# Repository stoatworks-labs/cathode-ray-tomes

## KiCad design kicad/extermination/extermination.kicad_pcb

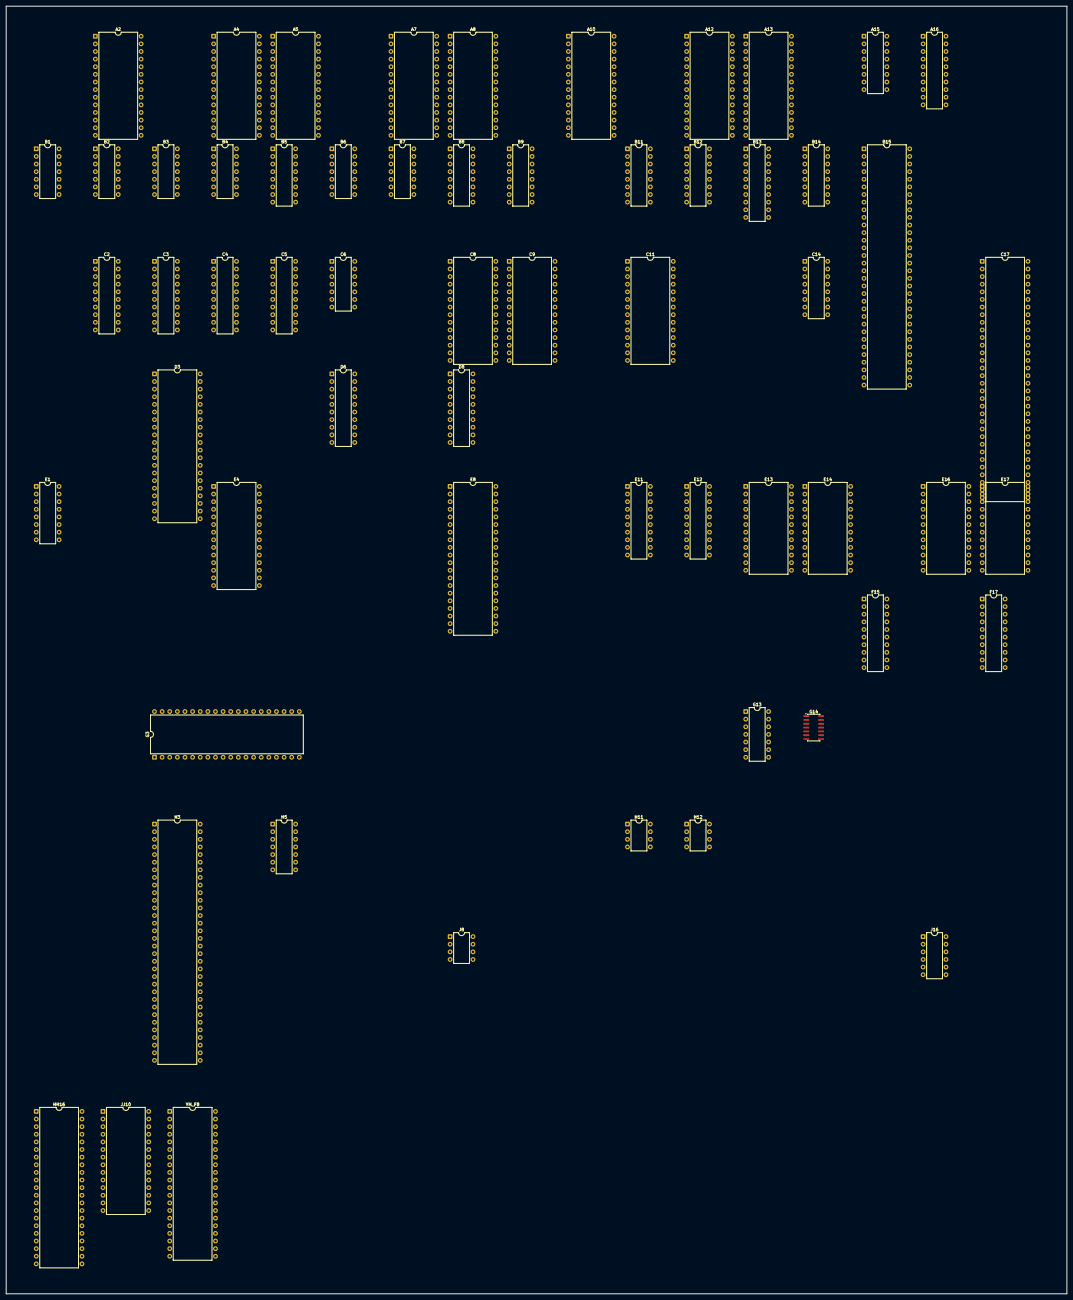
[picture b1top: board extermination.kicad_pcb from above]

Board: 2 copper layers, 353.4 x 429.0 mm, 60 parts (0 on the bottom side), 301 nets, no tracks yet.

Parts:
A2, A4, A5, A7, A8, A10, A12, A13: 27C512; DIP-28_W15.24mm
A15: 74LS174; DIP-16_W7.62mm
A16: 74LS273; DIP-20_W7.62mm
B1: 74LS04; DIP-14_W7.62mm
B2, B6: 74LS08; DIP-14_W7.62mm
B3, B4, B7: 74LS74; DIP-14_W7.62mm
B5: 74LS174; DIP-16_W7.62mm
B8, B9, B11, B12: 74LS157; DIP-16_W7.62mm
B13: 74LS245; DIP-20_W7.62mm
B14: 74LS367; DIP-16_W7.62mm
B15: YM3909; DIP-64_W15.24mm
C2, C3: PAL16L8; DIP-20_W7.62mm
C4, C5: 74LS245; DIP-20_W7.62mm
C6: 74LS32; DIP-14_W7.62mm
C8: MB8464A-10L-LL; DIP-28_W15.24mm
C9, C11: 27C512; DIP-28_W15.24mm
C14: 74LS367; DIP-16_W7.62mm
C17: YM3906; DIP-64_W15.24mm
D3: Z80CPU; DIP-40_W15.24mm
D6, D8: PAL16L8; DIP-20_W7.62mm
E1: 74LS174; DIP-16_W7.62mm
E4: 27C512; DIP-28_W15.24mm
E8: Z80CPU; DIP-40_W15.24mm
E11, E12: 74LS245; DIP-20_W7.62mm
E13, E14, E16, E17: HM6116P-3; DIP-24_W15.24mm
F15, F17: MB7124E; DIP-20_W7.62mm
G3: INTEL8742; DIP-40_W15.24mm
G13: 74LS04; DIP-14_W7.62mm
G14: 74HC4024; SOIC-14_3.9x8.7mm_P1.27mm
H3: SETA-X1-004; DIP-64_W15.24mm
H5: 74LS02; DIP-14_W7.62mm
H11: YM3014; DIP-8_W7.62mm
H12: NJM4558; DIP-8_W7.62mm
HH16: SETAX1-003; DIP-42_W15.24mm
J8: TL7705A; DIP-8_W7.62mm
J16: HA1388; DIP-12_W7.62mm
JJ10: PC050CM; DIP-28_W15.24mm
YM_F8: YM2203; DIP-40_W15.24mm

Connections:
/CI/O1: H3.23, JJ10.3
/CI/O2: H3.22, JJ10.14
/DATAEN: B15.4, C17.61
/GDA0: A12.11, A13.11, B15.56
/GDA1: A12.12, A13.12, B15.57
/GDA2: A12.13, A13.13, B15.58
/GDA3: A12.15, A13.15, B15.59
/GDA4: A12.16, A13.16, B15.60
/GDA5: A12.17, A13.17, B15.61
/GDA6: A12.18, A13.18, B15.62
/GDA7: A12.19, A13.19, B15.63
/GDB0: A8.11, A10.11, B15.48
/GDB1: A8.12, A10.12, B15.49
/GDB2: A8.13, A10.13, B15.50
/GDB3: A8.15, A10.15, B15.51
/GDB4: A8.16, A10.16, B15.52
/GDB5: A8.17, A10.17, B15.53
/GDB6: A8.18, A10.18, B15.54
/GDB7: A8.19, A10.19, B15.55
/GDC0: A5.11, A7.11, B15.40
/GDC1: A5.12, A7.12, B15.41
/GDC2: A5.13, A7.13, B15.42
/GDC3: A5.15, A7.15, B15.43
/GDC4: A5.16, A7.16, B15.44
/GDC5: A5.17, A7.17, B15.45
/GDC6: A5.18, A7.18, B15.46
/GDC7: A5.19, A7.19, B15.47
/GDD0: A2.11, A4.11, B15.30
/GDD1: A2.12, A4.12, B15.31
/GDD2: A2.13, A4.13, B15.34
/GDD3: A2.15, A4.15, B15.35
/GDD4: A2.16, A4.16, B15.36
/GDD5: A2.17, A4.17, B15.37
/GDD6: A2.18, A4.18, B15.38
/GDD7: A2.19, A4.19, B15.39
/GFXA_~CS: D6.18, E13.18
/GFXB_~CS: D6.17, E14.18
/GFXC_~CS: D6.16, E16.18
/GFXD_~CS: D6.15, E17.18
/GFX_CLK: B15.3, C17.62
/GFX_~CE: B6.6, C6.1
/H0: B13.4, B13.5, B13.6, C17.40
/H0_BUF: B3.3, B3.11, B7.11, B13.15, D3.6
/H1: B13.7, C17.39
/H1_BUF: B13.13, G3.2, G13.11
/H2: B13.2, C17.41
/H2_BUF: B2.4, B13.18, YM_F8.38
/H3: B1.1, B13.8, C17.42
/H3_BUF: B2.5, B13.12, B14.1, B14.15, C6.2, C6.13, C14.1, C14.15, D6.11
/H4: B13.9, C17.43
/H4_BUF: A15.9, A16.11, B13.11
/HC0: B15.19, C17.46
/HC1: B15.18, C17.47
/HC2: B15.17, C17.48
/HC3: B15.16, C17.49
/HC4: B15.15, C17.50
/HC5: B15.14, C17.51
/HC6: B15.13, C17.52
/HC7: B15.12, C17.53
/HC8: B15.11, C17.54
/MAIN_A0: B12.10, B14.10, C9.10, C11.10, E8.30
/MAIN_A1: B12.13, B14.12, C9.9, C11.9, E8.31
/MAIN_A2: B9.3, B14.14, C9.8, C11.8, E8.32
/MAIN_A3: B11.13, B14.2, C9.7, C11.7, E8.33
/MAIN_A4: B12.3, B14.4, C9.6, C11.6, E8.34
/MAIN_A5: B12.6, B14.6, C9.5, C11.5, E8.35
/MAIN_A6: B11.10, C9.4, C11.4, C14.4, E8.36
/MAIN_A7: B11.6, C9.3, C11.3, C14.6, E8.37
/MAIN_A8: B8.3, C9.25, C11.25, C14.10, E8.38
/MAIN_A9: B8.6, C9.24, C11.24, C14.12, D8.7, E8.39
/MAIN_A10: B9.10, C9.21, C11.21, C14.14, D8.6, E8.40
/MAIN_A11: B11.3, C9.23, C11.23, C17.27, D8.5, E8.1
/MAIN_A12: B9.13, C9.2, C11.2, D8.4, E8.2
/MAIN_A13: C8.26, C9.26, C11.26, D8.3, E8.3
/MAIN_A14: D6.2, D8.2, E8.4
/MAIN_A15: B2.10, D6.1, D8.1, E8.5
/MAIN_D0: E8.14, E11.3, E12.3
/MAIN_D1: E8.15, E11.2, E12.2
/MAIN_D2: E8.12, E11.9, E12.9
/MAIN_D3: E8.8, E11.8, E12.8
/MAIN_D4: E8.7, E11.7, E12.7
/MAIN_D5: E8.9, E11.6, E12.6
/MAIN_D6: E8.10, E11.5, E12.5
/MAIN_D7: E8.13, E11.4, E12.4
/MAIN_VD8: B5.3, C5.9, C9.11, C11.11
/MAIN_VD9: B5.4, C5.8, C9.12, C11.12
/MAIN_VD10: B5.6, C5.7, C9.13, C11.13
/MAIN_VD11: B5.14, C5.6, C9.15, C11.15
/MAIN_VD12: B5.13, C5.5, C9.16, C11.16
/MAIN_VD13: B5.11, C5.4, C9.17, C11.17
/MAIN_VD14: C5.3, C9.18, C11.18
/MAIN_VD15: C5.2, C9.19, C11.19
/MAIN_~RD: B1.9, B8.10, C5.1, C17.2, E8.21, E11.1, E12.1
/P10: G3.27, H3.28, H3.44
/P11: G3.28, H3.29, H3.45
/P12: G3.29, H3.30, H3.46
/P13: G3.30, H3.31, H3.47
/P14: G3.31, H3.32, H3.48
/P15: G3.32, H3.33, H3.49
/P16: G3.33, H3.34, H3.50
/P17: G3.34, H3.35, H3.51
/P20: G3.21, H3.37
/P21: G3.22, H3.41
/P22: G3.23, H3.40
/P26_DRQ: G3.37, H5.2
/RAM_~CS1: C3.17, C8.20
/RAM_~WE: C3.18, C8.27
/RESET: H5.3, H5.6, H5.9, H5.12, J8.6
/SND_A0: B12.11, D3.30, E4.10, G3.9, YM_F8.37
/SND_A1: B12.14, D3.31, E4.9
/SND_A2: B9.2, D3.32, E4.8
/SND_A3: B11.14, D3.33, E4.7
/SND_A4: B12.2, D3.34, E4.6
/SND_A5: B12.5, D3.35, E4.5
/SND_A6: B11.11, D3.36, E4.4
/SND_A7: B11.5, D3.37, E4.3
/SND_A8: B8.2, D3.38, E4.25
/SND_A9: B8.5, D3.39, E4.24
/SND_A10: B9.11, D3.40, E4.21
/SND_A11: B11.2, C2.5, D3.1, E4.23
/SND_A12: B9.14, C2.4, D3.2, E4.2
/SND_A13: C2.3, D3.3
/SND_A14: C2.2, D3.4
/SND_A15: C2.1, D3.5, E4.1
/SND_D0: C4.9, D3.14, E1.14, E4.11, G3.12, YM_F8.40
/SND_D1: C4.8, D3.15, E1.13, E4.12, G3.13, YM_F8.2
/SND_D2: C4.7, D3.12, E1.11, E4.13, G3.14, YM_F8.3
/SND_D3: C4.6, D3.8, E1.6, E4.15, G3.15, YM_F8.4
/SND_D4: C4.5, D3.7, E1.4, E4.16, G3.16, YM_F8.5
/SND_D5: C4.4, D3.9, E1.3, E4.17, G3.17, YM_F8.6
/SND_D6: C4.3, D3.10, E4.18, G3.18, YM_F8.7
/SND_D7: C4.2, D3.13, E4.19, G3.19, YM_F8.8
/SND_~RD: B8.11, C4.1, D3.21, G3.8, YM_F8.36
/SND_~WAIT: C3.13, D3.24
/SND_~WR: C2.6, C3.4, D3.22, G3.10, YM_F8.35
/SYNC: HH16.22, HH16.23
/VA0: B14.9, C17.15, E13.8, E14.8, E16.8, E17.8
/VA1: B14.11, C17.16, E13.7, E14.7, E16.7, E17.7
/VA2: B14.13, C17.17, E13.6, E14.6, E16.6, E17.6
/VA3: B14.3, C17.18, E13.5, E14.5, E16.5, E17.5
/VA4: B14.5, C17.19, E13.4, E14.4, E16.4, E17.4
/VA5: B14.7, C17.20, E13.3, E14.3, E16.3, E17.3
/VA6: C14.5, C17.21, E13.2, E14.2, E16.2, E17.2
/VA7: C14.7, C17.22, E13.1, E14.1, E16.1, E17.1
/VA8: C14.9, C17.23, E13.23, E14.23, E16.23, E17.23
/VA9: C14.11, C17.24, E13.22, E14.22, E16.22, E17.22
/VA10: C14.13, C17.25, E13.19, E14.19, E16.19, E17.19
/VA11: C17.28, D6.7
/VBLK: B1.12, B4.3
/VD0: A15.4, C17.4, E12.17, E13.9, E14.9
/VD1: A15.3, E12.18, E13.10, E14.10
/VD2: A15.14, B15.10, E12.11, E13.11, E14.11
/VD3: A15.13, B15.9, E12.12, E13.13, E14.13
/VD4: A15.11, B15.8, E12.13, E13.14, E14.14
/VD5: A15.6, B15.7, E12.14, E13.15, E14.15
/VD6: B15.6, C17.59, E12.15, E13.16, E14.16
/VD7: B15.5, C17.60, E12.16, E13.17, E14.17
/VD8: A16.14, C17.14, E11.17, E16.9, E17.9
/VD9: A16.17, C17.13, E11.18, E16.10, E17.10
/VD10: A16.3, C17.12, E11.11, E16.11, E17.11
/VD11: A16.4, C17.11, E11.12, E16.13, E17.13
/VD12: A16.7, C17.10, E11.13, E16.14, E17.14
/VD13: A16.8, C17.9, E11.14, E16.15, E17.15
/VD14: A16.13, C17.8, E11.15, E16.16, E17.16
/VD15: A16.18, C17.7, E11.16, E16.17, E17.17
/WATCHDOG: B1.6, G14.2
/colmix/COL0: B15.20, F15.1, F17.1
/colmix/COL1: B15.21, F15.2, F17.2
/colmix/COL2: B15.22, F15.3, F17.3
/colmix/COL3: B15.23, F15.4, F17.4
/colmix/COL4: B15.24, F15.5, F17.5
/colmix/COL5: B15.25, F15.16, F17.16
/colmix/COL6: B15.26, F15.17, F17.17
/colmix/COL7: B15.27, F15.18, F17.18
/colmix/COL8: B15.28, F15.19, F17.19
/gfx/GA0: A2.10, A4.10, A5.10, A7.10, A8.10, A10.10, A12.10, A13.10, C17.35
/gfx/GA1: A2.9, A4.9, A5.9, A7.9, A8.9, A10.9, A12.9, A13.9, C17.36
/gfx/GA2: A2.8, A4.8, A5.8, A7.8, A8.8, A10.8, A12.8, A13.8, C17.37
/gfx/GA4: A2.6, A4.6, A5.6, A7.6, A8.6, A10.6, A12.6, A13.6, C17.38
/gfx/GA5: A2.5, A4.5, A5.5, A7.5, A8.5, A10.5, A12.5, A13.5, A16.15
/gfx/GA6: A2.4, A4.4, A5.4, A7.4, A8.4, A10.4, A12.4, A13.4, A16.16
/gfx/GA7: A2.3, A4.3, A5.3, A7.3, A8.3, A10.3, A12.3, A13.3, A16.2
/gfx/GA8: A2.25, A4.25, A5.25, A7.25, A8.25, A10.25, A12.25, A13.25, A16.5
/gfx/GA9: A2.24, A4.24, A5.24, A7.24, A8.24, A10.24, A12.24, A13.24, A16.6
/gfx/GA10: A2.21, A4.21, A5.21, A7.21, A8.21, A10.21, A12.21, A13.21, A16.9
/gfx/GA11: A2.23, A4.23, A5.23, A7.23, A8.23, A10.23, A12.23, A13.23, A16.12
/gfx/GA12: A2.2, A4.2, A5.2, A7.2, A8.2, A10.2, A12.2, A13.2, A16.19
/gfx/GA13: A2.26, A4.26, A5.26, A7.26, A8.26, A10.26, A12.26, A13.26, A15.5
/gfx/GA14: A2.27, A4.27, A5.27, A7.27, A8.27, A10.27, A12.27, A13.27, A15.2
/gfx/GA15: A2.1, A4.1, A5.1, A7.1, A8.1, A10.1, A12.1, A13.1, A15.12
/gfx/GFX_~WR: C6.6, E13.21, E14.21, E16.21, E17.21
/gfx/HR8: A2.7, A4.7, A5.7, A7.7, A8.7, A10.7, A12.7, A13.7, C17.34
/gfx/SPBANK1: C14.3, C17.26
/gfx/gfx_rom/~ROM_CE': A2.20, A5.20, A8.20, A12.20, B1.10
/gfx/~ROM_CE: A4.20, A7.20, A10.20, A13.20, A15.10, B1.11
/gfx/~ROM_OE: A2.22, A4.22, A5.22, A7.22, A8.22, A10.22, A12.22, A13.22, A15.15
/main/BANK_CFG0: B5.2, C9.27, D6.6
/main/BANK_CFG1: B2.9, B5.5, C9.1
/main/BANK_CFG2: B5.7, D6.5
/main/MAIN_~WAIT: C3.14, E8.24
/main/MAIN_~WR: C3.2, D8.11, E8.22
/main/ROMB_A14: C11.27, D6.14
/main/ROMB_A15: B2.8, C11.1
/main/~BGTRNSP: B6.4, D8.14
/main/~MREQ: D6.3, D8.8, E8.19
/main/~OBJCODEHI: B6.5, D6.9, D8.17
/main/~RFSH: D6.4, D8.9, E8.28
/main/~RM_OEA: C9.22, D6.12
/main/~RM_OEB: C11.22, D6.13
/main/~SND_RST': B2.2, B5.12
/main/~WDOGCLR: B1.5, B5.9, D8.15
/mcu/TEST0: G3.1, JJ10.25
/mcu/TEST1: G3.39, JJ10.26
/mcu/~H1_BUF: G3.3, G13.10
/sound/RAM_~OE: B8.9, C8.22
/sound/SHA0: B12.9, C8.10
/sound/SHA1: B12.12, C8.9
/sound/SHA2: B9.4, C8.8
/sound/SHA3: B11.12, C8.7
/sound/SHA4: B12.4, C8.6
/sound/SHA5: B12.7, C8.5
/sound/SHA6: B11.9, C8.4
/sound/SHA7: B11.7, C8.3
/sound/SHA8: B8.4, C8.25
/sound/SHA9: B8.7, C8.24
/sound/SHA10: B9.9, C8.21
/sound/SHA11: B11.4, C8.23
/sound/SHA12: B9.12, C8.2
/sound/SHD0: C4.11, C5.11, C8.11
/sound/SHD1: C4.12, C5.12, C8.12
/sound/SHD2: C4.13, C5.13, C8.13
/sound/SHD3: C4.14, C5.14, C8.15
/sound/SHD4: C4.15, C5.15, C8.16
/sound/SHD5: C4.16, C5.16, C8.17
/sound/SHD6: C4.17, C5.17, C8.18
/sound/SHD7: C4.18, C5.18, C8.19
/sound/SND_CLK': B3.4, B3.9
/sound/SND_D'0: C2.11, E1.15
/sound/SND_D'1: C2.9, E1.12
/sound/SND_~INT: B7.8, D3.16
/sound/SND_~NMI: D3.17, YM_F8.25
/sound/SND_~OE: C2.12, E4.22
/sound/SND_~RFSH: C2.8, D3.28
/sound/S_~IORQ: B7.13, D3.20
/sound/S_~MREQ: C2.7, D3.19
/sound/YM_~CS: B3.2, C2.15, YM_F8.34
/sound/~SND_A14: C2.18, E4.26
/sound/~SND_A15: C2.19, E4.27
/sound/~SND_WR: C2.14, E1.9
/~COIN_LOCK: H5.1, JJ10.23
/~GFX_WR: B6.1, C17.3, D8.13
/~HBLK: C17.55, HH16.19
/~MCU_RST: B2.11, G3.4
/~OBJCODELO: B6.2, D6.8, D8.16
/~SBNKMWR: C3.16, C5.19
/~SBNKSWR: C3.15, C4.19
/~SND_CS: C2.16, G3.6
/~SND_MREQ: C2.13, C3.3
/~SND_RST: B2.3, B2.12, D3.26, E1.1, YM_F8.24
/~SND_SELECT: B8.1, B9.1, B11.1, B12.1, C3.19
/~VSYNC: C17.56, HH16.20
/~WDRES: B2.1, B5.1, C17.29, E8.26
unnamed: B1.8, C6.4
unnamed: B3.5, B3.12
unnamed: B4.6, E8.16
unnamed: B4.1, E8.20
unnamed: B2.6, B4.12
unnamed: B4.9, C3.6
unnamed: B6.3, C6.12
unnamed: B4.11, B13.17, E8.6
unnamed: C3.1, D8.18
unnamed: C3.5, D8.19
unnamed: C6.5, C17.30
unnamed: B1.13, C17.58
unnamed: G13.1, G13.4
unnamed: B2.13, E1.5
unnamed: C6.11, E11.19
unnamed: C6.3, E12.19
unnamed: G3.35, H5.11
unnamed: G3.36, H5.8
unnamed: G3.38, H5.5
unnamed: G13.3, G13.12
unnamed: G13.9, G14.5
unnamed: G13.2, G14.1
unnamed: H11.2, H12.3
unnamed: H11.3, YM_F8.22
unnamed: H11.8, H12.6, H12.7
unnamed: H11.5, YM_F8.39
unnamed: H11.7, H12.5
unnamed: H11.4, YM_F8.23
unnamed: H12.1, H12.2
unnamed: H5.4, JJ10.20
unnamed: H5.10, JJ10.8
unnamed: H5.13, JJ10.17
unnamed: YM_F8.18, YM_F8.19, YM_F8.20
unnamed: YM_F8.26, YM_F8.27
unnamed: YM_F8.28, YM_F8.29
unnamed: YM_F8.30, YM_F8.31
unnamed: YM_F8.32, YM_F8.33
VCC: A2.28, A4.28, A5.28, A7.28, A8.28, A10.28, A12.28, A13.28, A15.1, A16.1, B1.14, B2.14, B3.1, B3.10, B3.13, B3.14, B4.2, B4.4, B4.10, B4.13, B4.14, B6.14, B7.10, B7.12, B7.14, B13.1, B15.1, B15.33, C2.20, C3.20, C6.14, C8.28, C9.28, C11.28, C17.1, C17.33, D3.11, D6.20, D8.20, E4.28, E8.11, E8.17, E13.24, E14.24, E16.24, E17.24, F15.20, F17.20, G3.5, G3.26, G3.40, G13.14, G14.14, H3.27, H3.53, H5.14, H11.1, H12.8, HH16.18, HH16.42, J8.8, J16.10, JJ10.5, JJ10.9, JJ10.21, YM_F8.21
VSS: A2.14, A4.14, A5.14, A7.14, A8.14, A10.14, A12.14, A13.14, B1.7, B2.7, B3.7, B4.7, B6.7, B7.7, B8.15, B9.15, B11.15, B12.15, B13.19, B15.32, B15.64, C2.10, C3.10, C6.7, C8.14, C9.14, C9.20, C11.14, C11.20, C17.5, C17.6, C17.32, C17.64, D3.29, D6.10, D8.10, E4.14, E4.20, E8.29, E13.12, E13.20, E14.12, E14.20, E16.12, E16.20, E17.12, E17.20, F15.10, F15.15, F17.10, F17.15, G3.7, G3.20, G13.7, G14.7, H3.1, H3.18, H3.19, H3.20, H3.21, H3.36, H3.38, H3.39, H3.42, H3.43, H3.52, H5.7, H11.6, H12.4, HH16.21, J8.4, J16.4, J16.9, JJ10.1, JJ10.6, JJ10.11, JJ10.15, JJ10.24, YM_F8.1
